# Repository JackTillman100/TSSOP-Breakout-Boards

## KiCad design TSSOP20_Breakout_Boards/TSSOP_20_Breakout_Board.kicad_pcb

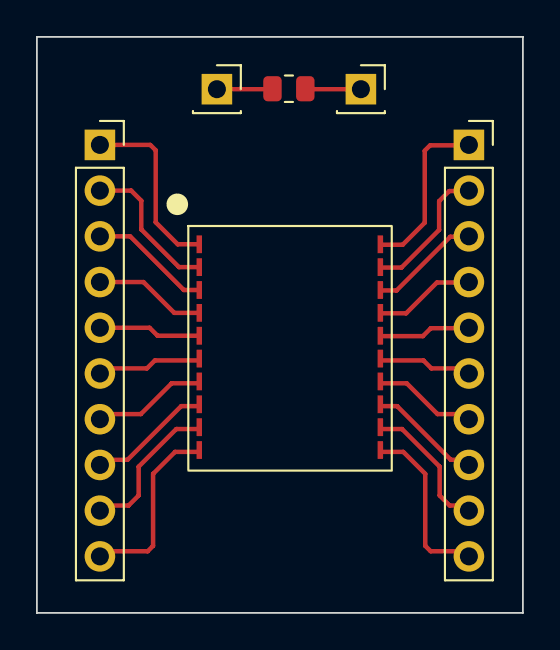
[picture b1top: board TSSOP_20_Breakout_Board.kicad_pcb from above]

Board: 2 copper layers, 27.0 x 32.0 mm, 6 parts (0 on the bottom side), 22 nets.

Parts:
J1, J2: Conn_01x10; PinSocket_1x10_P2.54mm_Vertical
J3, J4: Conn_01x01; PinSocket_1x01_P2.54mm_Vertical
R1: R_US; R_0805_2012Metric
TSSOP20: 20_Pin_TSSOP_Board

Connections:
unnamed: J1.1, TSSOP20.1
unnamed: J1.2, TSSOP20.2
unnamed: J1.3, TSSOP20.3
unnamed: J1.4, TSSOP20.4
unnamed: J1.5, TSSOP20.5
unnamed: J1.6, TSSOP20.6
unnamed: J1.7, TSSOP20.7
unnamed: J1.8, TSSOP20.8
unnamed: J1.9, TSSOP20.9
unnamed: J1.10, TSSOP20.10
unnamed: J2.1, TSSOP20.20
unnamed: J2.2, TSSOP20.19
unnamed: J2.3, TSSOP20.18
unnamed: J2.4, TSSOP20.17
unnamed: J2.5, TSSOP20.16
unnamed: J2.6, TSSOP20.15
unnamed: J2.7, TSSOP20.14
unnamed: J2.8, TSSOP20.13
unnamed: J2.9, TSSOP20.12
unnamed: J2.10, TSSOP20.11
unnamed: J3.1, R1.2
unnamed: J4.1, R1.1

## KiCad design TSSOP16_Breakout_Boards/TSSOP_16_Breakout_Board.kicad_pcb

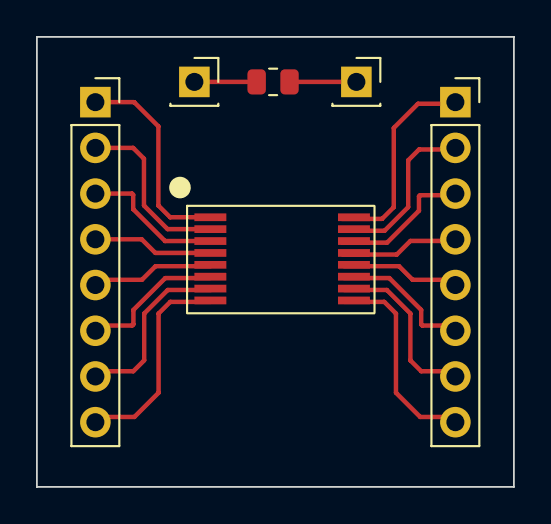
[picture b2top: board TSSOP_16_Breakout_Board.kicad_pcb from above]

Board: 2 copper layers, 26.5 x 25.0 mm, 6 parts (0 on the bottom side), 18 nets.

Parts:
J1, J2: Conn_01x08; PinSocket_1x08_P2.54mm_Vertical
J3, J4: Conn_01x01; PinSocket_1x01_P2.54mm_Vertical
R1: R_US; R_0805_2012Metric
TSSOP16: 16_Pin_TSSOP_Board

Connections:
unnamed: J1.1, TSSOP16.1
unnamed: J1.2, TSSOP16.2
unnamed: J1.3, TSSOP16.3
unnamed: J1.4, TSSOP16.4
unnamed: J1.5, TSSOP16.5
unnamed: J1.6, TSSOP16.6
unnamed: J1.7, TSSOP16.7
unnamed: J1.8, TSSOP16.8
unnamed: J2.1, TSSOP16.16
unnamed: J2.2, TSSOP16.15
unnamed: J2.3, TSSOP16.14
unnamed: J2.4, TSSOP16.13
unnamed: J2.5, TSSOP16.12
unnamed: J2.6, TSSOP16.11
unnamed: J2.7, TSSOP16.10
unnamed: J2.8, TSSOP16.9
unnamed: J3.1, R1.2
unnamed: J4.1, R1.1

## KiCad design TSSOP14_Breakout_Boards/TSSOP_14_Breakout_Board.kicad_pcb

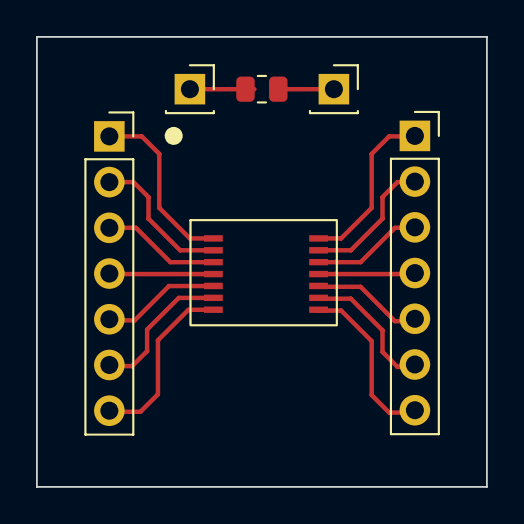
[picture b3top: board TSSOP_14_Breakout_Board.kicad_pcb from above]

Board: 2 copper layers, 25.0 x 25.0 mm, 6 parts (0 on the bottom side), 16 nets.

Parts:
J1, J2: Conn_01x07; PinSocket_1x07_P2.54mm_Vertical
J3, J4: Conn_01x01; PinSocket_1x01_P2.54mm_Vertical
R1: R_US; R_0805_2012Metric
TSSOP14: 14_Pin_TSSOP_Board

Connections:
unnamed: J1.1, TSSOP14.1
unnamed: J1.2, TSSOP14.2
unnamed: J1.3, TSSOP14.3
unnamed: J1.4, TSSOP14.4
unnamed: J1.5, TSSOP14.5
unnamed: J1.6, TSSOP14.6
unnamed: J1.7, TSSOP14.7
unnamed: J2.1, TSSOP14.14
unnamed: J2.2, TSSOP14.13
unnamed: J2.3, TSSOP14.12
unnamed: J2.4, TSSOP14.11
unnamed: J2.5, TSSOP14.10
unnamed: J2.6, TSSOP14.9
unnamed: J2.7, TSSOP14.8
unnamed: J3.1, R1.2
unnamed: J4.1, R1.1

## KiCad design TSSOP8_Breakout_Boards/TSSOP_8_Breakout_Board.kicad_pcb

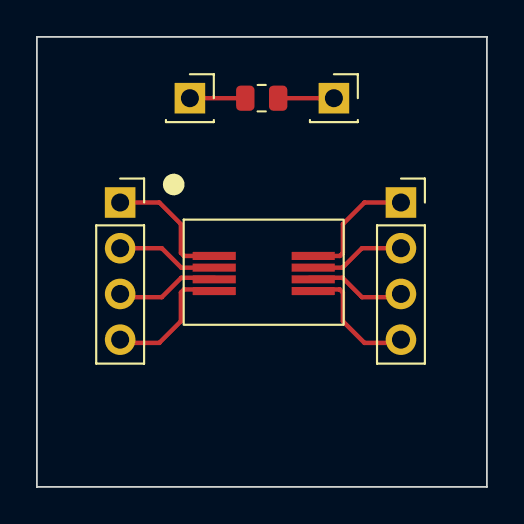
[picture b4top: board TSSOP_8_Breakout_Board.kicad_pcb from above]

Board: 2 copper layers, 25.0 x 25.0 mm, 6 parts (0 on the bottom side), 10 nets.

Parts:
J1, J2: Conn_01x04; PinSocket_1x04_P2.54mm_Vertical
J3, J4: Conn_01x01; PinSocket_1x01_P2.54mm_Vertical
R1: R_US; R_0805_2012Metric
TSSOP8: 8_Pin_TSSOP; 8_Pin_TSSOP_Board

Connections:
unnamed: J1.1, TSSOP8.1
unnamed: J1.2, TSSOP8.2
unnamed: J1.3, TSSOP8.3
unnamed: J1.4, TSSOP8.4
unnamed: J2.1, TSSOP8.8
unnamed: J2.2, TSSOP8.7
unnamed: J2.3, TSSOP8.6
unnamed: J2.4, TSSOP8.5
unnamed: J3.1, R1.2
unnamed: J4.1, R1.1

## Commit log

2023-04-05 Testing
    test file - disregard
2023-04-05 deleted testing files
    deleted files to see how it affects repo
2023-05-09 created folders for the 4 tssop breakout boards
    finalized the tssop 8 breakout board
2023-05-09 TSSOP14
    created kicad files for the tssop 14 breakout board
2023-05-10 tssop 16 & 20 boards
    initialized files for the tssop 16 and 20 boards and finalized their schematics
2023-05-10 progress on tssop 16 board
2023-05-10 finalized tssop 16 board
2023-05-10 finalized tssop 20 design
2023-06-02 final commit
